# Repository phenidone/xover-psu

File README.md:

# Preamp Power Supply

This is a PCB design for an analogue preamplifier power supply

## Inputs

Power can be provided as one of:
* high voltage (240V) AC, relay-switched
* high voltage (240V) AC, unswitched,
* low voltage (20+20V) unregulated DC

An opto-isolated input (5-24V DC) is provided to control the power-switching relay.  Low-power (2A) switched AC loads can be
connected via terminals on the PCB, and high power loads (20A) can be switched using spade terminals on the rear of the 
relay.

If the PCB transformer is omitted, unregulated dual-rail DC can be fed into the linear regulator section.  Additional
filter capacitors may also be inserted at this point.  The unmute circuit will NOT work unless the transformer is present or
low-voltage AC is otherwise supplied to the board.

## Outputs

The circuit provides:
* +/- 12-15VDC, linear regulated
* 12VDC from always-on switchmode brick, for control circuits
* un-muting relay output
* 50Hz opto-isolated pulses for external power-sensing logic
* power-relay output

The power-relay terminals can be used as an output port to drive an external
relay, or can be used as an input port to drive the onboard relay if the
remote/relay driver circuit (U2, Q1, etc) is not populated.

The 12VDC output terminal could be used as an input from an external plugpack
if the HLK10M12 is not present.

### Unmute Logic

The UNMUTE output is designed to switch a 12V muting relay and thereby suppress bad noises that occur during power-up/down
brownout of preamplifier and power-amplifier circuits.

The unmute logic uses a slow turn-on RC timer and a fast turn-off RC timer, both of which are charged from opto-isolated pulses
derived from the mains transformer secondary.  The UNMUTE output (12VDC up to 500mA) is enabled after the slow timer charges, 
which is about 1s after power is applied; for a shorter turn-on delay, reduce the value of R2 and/or C1.

When power is withdrawn, the fast timer discharges in about 50ms, which causes Q2 to discharge the C in the slow timer,
thereby immediately shutting off the UNMUTE output and resetting the startup time.

Each RC timer uses a TL431 to provide a distinct transition point, for fast(ish) turn-on/off transitions.

A secondary AC pulse output is provided as bare optoisolator pins, allowing an external logic circuit to safely monitor the presence of AC
power going into the linear regulator.

### Linear Regulation

The dual-rail DC output is designed to power opamp-based preamplifier circuits and as such, has an output of approx 12-15V
DC depending on resistor selection choices.  The circuit should be good for about 250mA, depending on the transformer regulation.

## Construction

The board is very densely populated, and on both sides.  First assemble all the surface-mount components on the board front,
then install all through-hole components (except screw terminals) on the board rear.

### Errata

The pinouts of some TL431 devices have pins 1 and 2 reversed, i.e. they are mis-marked TL432s.  You can, with a little bending
of their leads, install those upside down and it will work.  The layout assumes the pin order is 1=K, 2=R, 3=A.

### Component Sourcing

The major/expensive items required are:
* TE T9GS1L24-12 power relay
* HiLink 10M12 AC/DC switchmode brick
* Vigortronix VTX-120-5412-415 transformer for 15V operation
    * alternative: VTX-120-5412-412 for 12V operation
    * alternative: Block PT-13/2/12 which has a similar footprint
* Bourns PM3700 common-mode choke
* Rectifier filter caps: Panasonic EEEFK 3300u or similar 18mm square electrolytics
* Other silicon and passives - buy it on eBay from China

An 0805 passive sample book is very handy for filling out most of the circuit; low-noise/precision values are not required.

### Output Voltage

Output voltage is selected by voltage dividers on the LM317 and LM337.  
Choose R18 and R28 to be 240R or 270R, then select values for R20 and R23
so that

> R20 = R18 (VOUT / 1.25 - 1)

If R20 is not a convenient value, make a parallel combination e.g. 5k1 and 6k8
in lieu of 3k to get about 15V.

### Regulator Caps

Regulator output capacitors should preferably be tantalum or aluminium electrolytic.
You can use either C6/C14 (SMD) or C7/C15 (through hole) footprints.  Make 
sure the capacitors are rated for notably more than the output voltage, 
e.g. 25V.

Ceramic caps here will cause regulator instability and oscillation.

### Pi Filter

The rectifier filter is a C-R-C pi-filter with 3300u per side.  Choose the resistors (R31, R26 etc) so that
the net voltage drop across them is as much as you can handle, without:
* bringing the unregulated DC rail so low that ripple breaks through the regulators, or
* the resistors overheating (max 100mW each) at your max design-load current

Larger resistors will provide greater ripple smoothing, at the expense of lower voltage
input to the regulators.  Choice will depend on your selection of transformer voltage, 
output voltage, and max expected load current.  A 15V supply has more room here for 
voltage drop (and therefore smoothing) than a 12V supply does.

Bridge them with 0R if you want a simple capacitor-only rectification filter.  Loading all
eight with 10R is probably OK for a 250mA output and will lose you about 0.65V DC and 160mW per rail.

### AC bits

The MOVs and common-mode choke are probably not critical.  Bridge over the 
choke if you're feeling EMI-antisocial, though this may result in HF conducted
EMI reaching your regulated outputs.

Use 500mA M205 slow blow glass fuses; there is one for each of the switchmode and
linear-regulated parts of the supply.  The switched-AC output is not fused, and should be good for 
about 5A before there are issues with terminal blocks.  For switching high-power amplifiers, use the
spade connectors on the rear of the relay.

### Grounding

There are three separate grounds:
* AGND, the centre of the dual-regulated supply
* DGND, ground for the 12V VDD switchmode/logic/control supply
* EARTH, a chassis safety connection

AGND is connected to EARTH via four opposed diodes in a bridge configuration,
which will keep them to no more than about 1.4V apart, but otherwise uncoupled
with respect to noise.

DGND is connected to EARTH via two opposed diodes and a capacitor.  They may
be up to 0.7V apart, and noise from the DC side of the 10M12 should be 
conducted into EARTH via C18.  These ground-lift circuits should be strong 
enough to trip an ELCB if there is a transformer-isolation fault that brings
mains AC power to the low voltage side.

The Vigortronix transformers have exposed steel cores which must be grounded via
mounting screws through the PCB, which are connected via the PCB to the 
EARTH screw terminal.

### PCB

Use a full-thickness (16.mm) PCB; 1mm boards are too flimsy with all of the heavy power supply components mounted.

## TRL and Regulatory

This design is tested and working in a benign environment at Rev.A.  It has not faced MTBF validation,
environmental (thermal+vibration) or EMI compliance testing.

In terms of electrical safety, this design
* is intended for use in Class I (grounded) equipment:
    * a safety-ground connection is mandatory,
    * it must be installed inside an IEC-60950 grounded case per Class I;
* additionally aims to comply with IEC-60950 "reinforced insulation" creepage+clearance rules,
* uses diode-based ground-lift circuits that may not be legal in all jurisdictions for a Class I device,

The design has not been certified by any regulatory body or independent third party testing agency.  You must 
not sell any product containing this power supply without first obtaining certification.

## License

This hardware design is (C) 2021 William Brodie-Tyrrell and is licensed under the CERN OHL; see cern_ohl_v_1_2.pdf

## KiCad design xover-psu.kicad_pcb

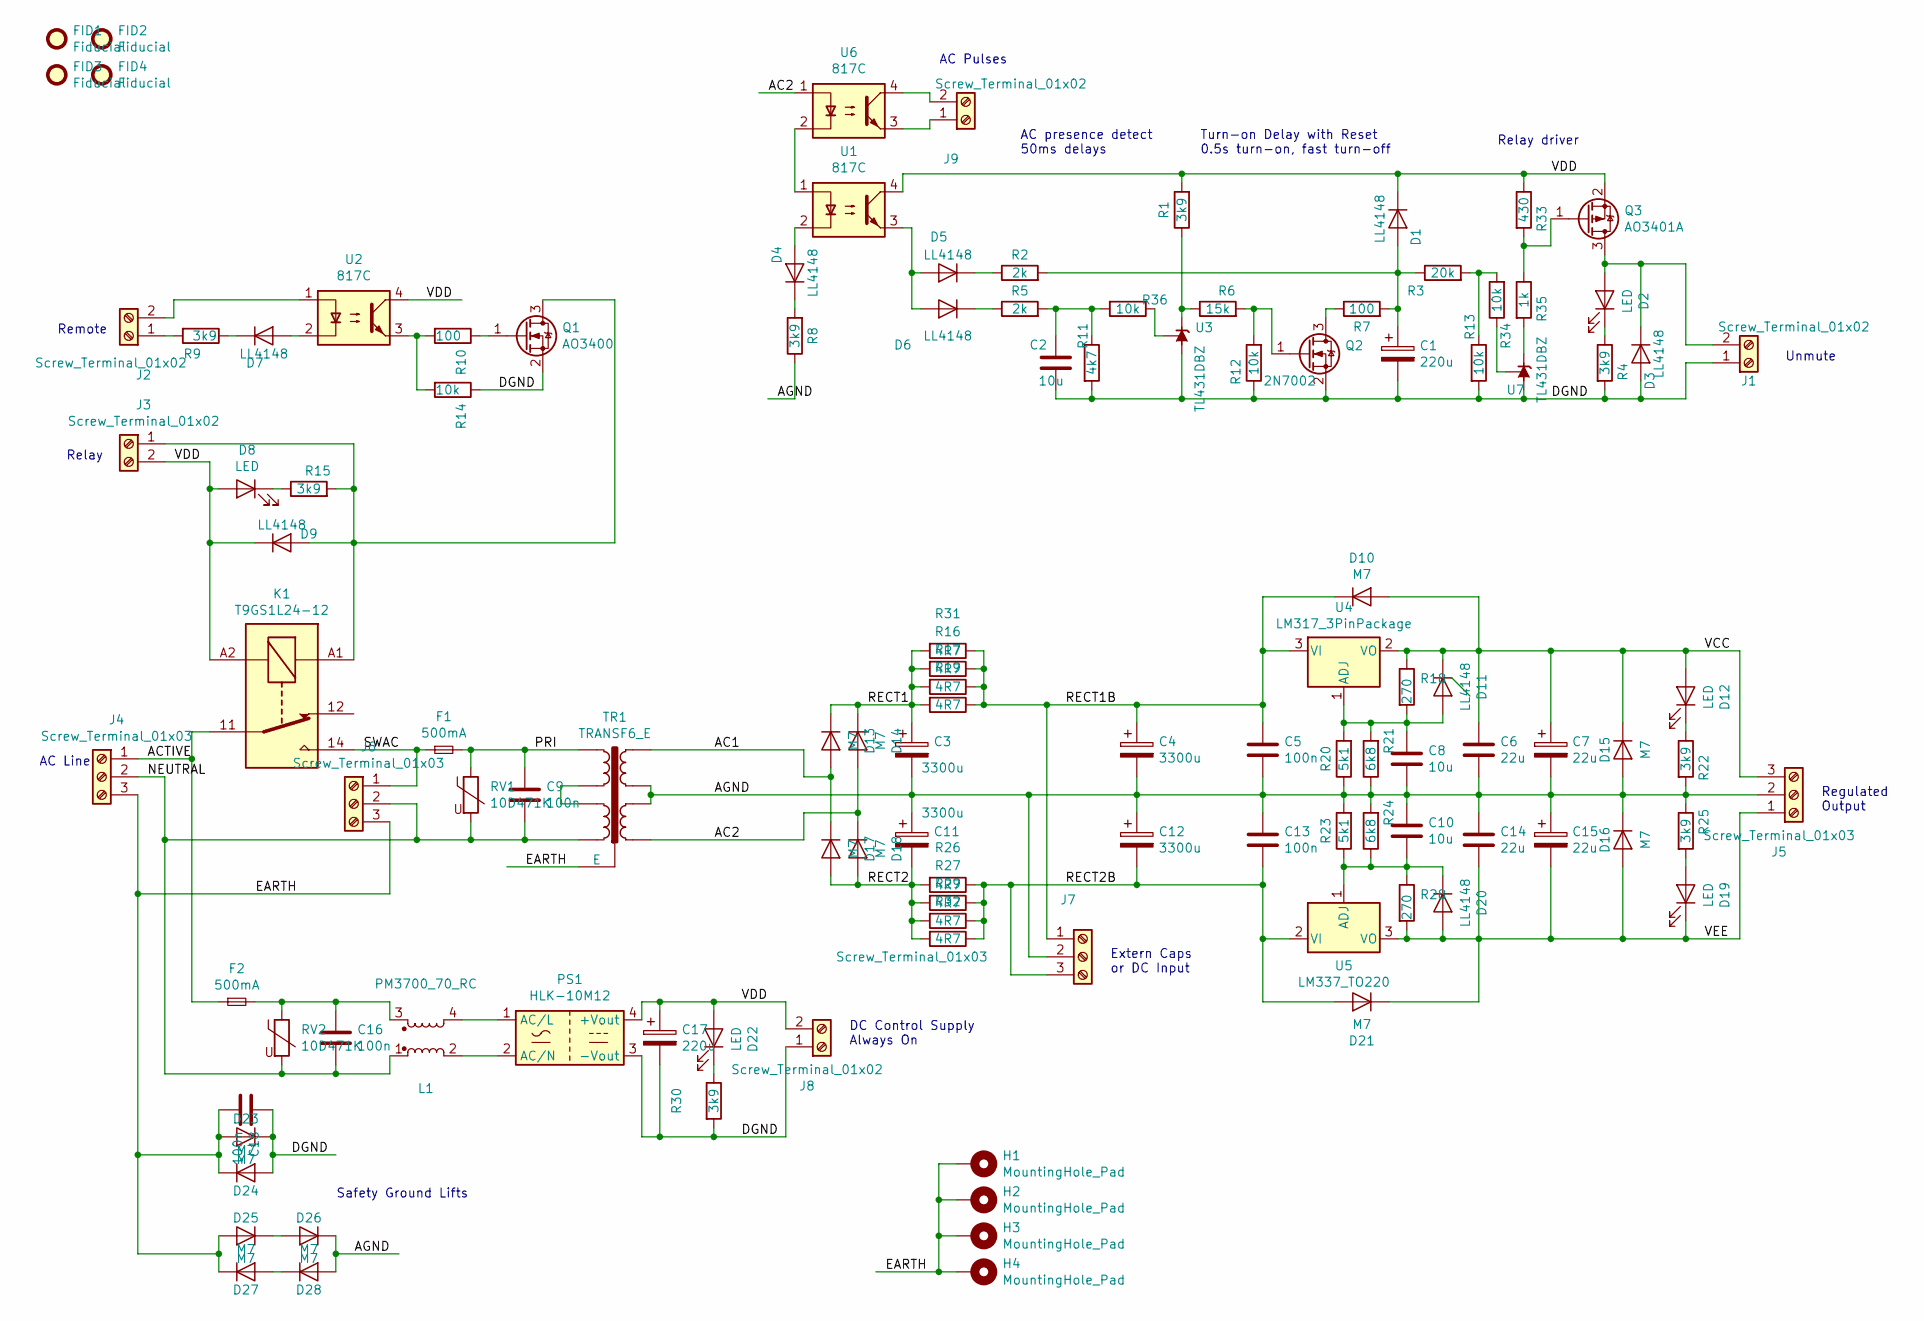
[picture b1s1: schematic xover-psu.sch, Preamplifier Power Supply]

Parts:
C1, C17: 220u; CP_Elec_10x10; MFG Part Num EEEFP1H221AP
C2, C8, C10: 10u; C_1210
C3, C4, C11, C12: 3300u; CP_Elec_EEEFK-K16
C5, C13, C18: 100n; C_0805
C6, C14: 22u; C_1210_HandSoldering
C7, C15: 22u; CP_Radial_Tantal_D6.0mm_P5.00mm
C9, C16: 100n; C_Rect_L18.0mm_W6.0mm_P15.00mm_FKS3_FKP3; MFG Part Num ECQU2A104KLA
D1, D3, D4, D5, D6, D7, D9, D11, D20: LL4148; D_MiniMELF
D2, D8, D12, D19, D22: LED; LED_0805
D10, D13, D14, D15, D16, D17, D18, D21, D23, D24, D25, D26, D27, D28: M7; D_SMA
F1, F2: 500mA; Fuseholder5x20_6mm
FID1, FID2, FID3, FID4: Fiducial; Fiducial_1mm_Dia_2.54mm_Outer_CopperTop
H1, H2, H3, H4: MountingHole_Pad; MountingHole_3.2mm_M3_DIN965_Pad
J1, J2, J3, J8, J9: Screw_Terminal_01x02; TerminalBlock_Phoenix_MKDS1.5-2pol
J4, J5, J6, J7: Screw_Terminal_01x03; TerminalBlock_Phoenix_MKDS1.5-3pol
K1: T9GS1L24-12; Potter_T9G_Relay
L1: PM3700_70_RC; PM3700
PS1: HLK-10M12
Q1: AO3400; SOT-23
Q2: 2N7002; SOT-23
Q3: AO3401A; SOT-23
R1, R4, R8, R9, R15, R22, R25, R30: 3k9; R_0805
R2, R5: 2k; R_0805
R3: 20k; R_0805
R6: 15k; R_0805
R7, R10: 100; R_0805
R11: 4k7; R_0805
R12, R13, R14, R34, R36: 10k; R_0805
R16, R17, R19, R26, R27, R29, R31, R32: 4R7; R_0805
R18, R28: 270; R_0805
R20, R23: 5k1; R_0805
R21, R24: 6k8; R_0805
R33: 430; R_0805
R35: 1k; R_0805
RV1, RV2: 10D471K; RV_Disc_D12_W3.9_P7.5
TR1: TRANSF6_E; Trafo_CHK-EI54-12VA_Combo_Vigor
U1, U2, U6: 817C; DIP-4_W7.62mm
U3, U7: TL431DBZ; SOT-23
U4: LM317_3PinPackage; TO-220-3_Vertical
U5: LM337_TO220; TO-220-3_Vertical

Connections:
/AC1: D13.2 (A), D17.1 (K), TR1.5
/AC2: D14.2 (A), D18.1 (K), TR1.8, U6.1
/ACTIVE: F2.1, J4.1, K1.11
/AGND: C3.2, C4.2, C5.2, C6.2, C7.2, C8.2, C10.1, C11.1, C12.1, C13.1, C14.1, C15.1, D15.2 (A), D16.1 (K), D26.1 (K), D28.2 (A), J5.2, J7.2, R8.1, R20.1, R21.1, R22.2, R23.2, R24.2, R25.1, TR1.6, TR1.7
/DGND: C1.2, C2.2, C17.2, C18.1, D3.2 (A), D23.1 (K), D24.2 (A), J1.1, J8.1, PS1.3 (-Vout), Q1.2 (S), Q2.2 (S), R4.2, R11.2, R12.1, R13.2, R14.1, R30.2, U3.3 (A), U7.3 (A)
/EARTH: C18.2, D23.2 (A), D24.1 (K), D25.2 (A), D27.1 (K), H1.1, H2.1, H3.1, H4.1, J4.3, J6.3, TR1.E
/NEUTRAL: C9.2, C16.2, J4.2, J6.2, L1.1, RV1.2, RV2.2, TR1.1
/PRI: C9.1, F1.2, RV1.1, TR1.4
/RECT1: C3.1, D13.1 (K), D14.1 (K), R16.2, R17.2, R19.2, R31.2
/RECT1B: C4.1, C5.1, D10.1 (K), J7.1, R16.1, R17.1, R19.1, R31.1, U4.3 (VI)
/RECT2: C11.2, D17.2 (A), D18.2 (A), R26.2, R27.2, R29.2, R32.2
/RECT2B: C12.2, C13.2, D21.2 (A), J7.3, R26.1, R27.1, R29.1, R32.1, U5.2 (VI)
/SWAC: F1.1, J6.1, K1.14
/VCC: C6.1, C7.1, D10.2 (A), D11.1 (K), D12.2 (A), D15.1 (K), J5.3, R18.1, U4.2 (VO)
/VDD: C17.1, D1.1 (K), D8.2 (A), D9.1 (K), D22.2 (A), J3.2, J8.2, K1.A2, PS1.4 (+Vout), Q3.2 (S), R1.2, R33.1, U1.4, U2.4
/VEE: C14.2, C15.2, D16.2 (A), D19.1 (K), D20.2 (A), D21.1 (K), J5.1, R28.2, U5.3 (VO)
unnamed: C1.1, D1.2 (A), R2.2, R3.1, R7.2
unnamed: C2.1, R5.2, R11.1, R36.2
unnamed: C8.1, D11.2 (A), R18.2, R20.2, R21.2, U4.1 (ADJ)
unnamed: C10.2, D20.1 (K), R23.1, R24.1, R28.1, U5.1 (ADJ)
unnamed: C16.1, F2.2, L1.3, RV2.1
unnamed: D2.1 (K), R4.1
unnamed: D2.2 (A), D3.1 (K), J1.2, Q3.3 (D)
unnamed: D4.1 (K), R8.2
unnamed: D4.2 (A), U1.2
unnamed: D5.1 (K), R2.1
unnamed: D5.2 (A), D6.2 (A), U1.3
unnamed: D6.1 (K), R5.1
unnamed: D7.1 (K), R9.1
unnamed: D7.2 (A), U2.2
unnamed: D8.1 (K), R15.1
unnamed: D9.2 (A), J3.1, K1.A1, Q1.3 (D), R15.2
unnamed: D12.1 (K), R22.1
unnamed: D19.2 (A), R25.2
unnamed: D22.1 (K), R30.1
unnamed: D25.1 (K), D26.2 (A)
unnamed: D27.2 (A), D28.1 (K)
unnamed: J2.1, R9.2
unnamed: J2.2, U2.1
unnamed: J9.1, U6.3
unnamed: J9.2, U6.4
unnamed: L1.2, PS1.2 (AC/N)
unnamed: L1.4, PS1.1 (AC/L)
unnamed: Q1.1 (G), R10.1
unnamed: Q2.1 (G), R6.2, R12.2
unnamed: Q2.3 (D), R7.1
unnamed: Q3.1 (G), R33.2, R35.1
unnamed: R1.1, R6.1, U3.1 (K)
unnamed: R10.2, R14.2, U2.3
unnamed: R3.2, R13.1, R34.2
unnamed: R34.1, U7.2 (REF)
unnamed: R35.2, U7.1 (K)
unnamed: R36.1, U3.2 (REF)
unnamed: TR1.2, TR1.3
unnamed: U1.1, U6.2

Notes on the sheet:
Regulated Output
DC Control Supply Always On
Relay
AC Line
Remote
Turn-on Delay with Reset 0.5s turn-on, fast turn-off
Relay driver
AC presence detect 50ms delays
Safety Ground Lifts
Extern Caps or DC Input
Unmute
AC Pulses

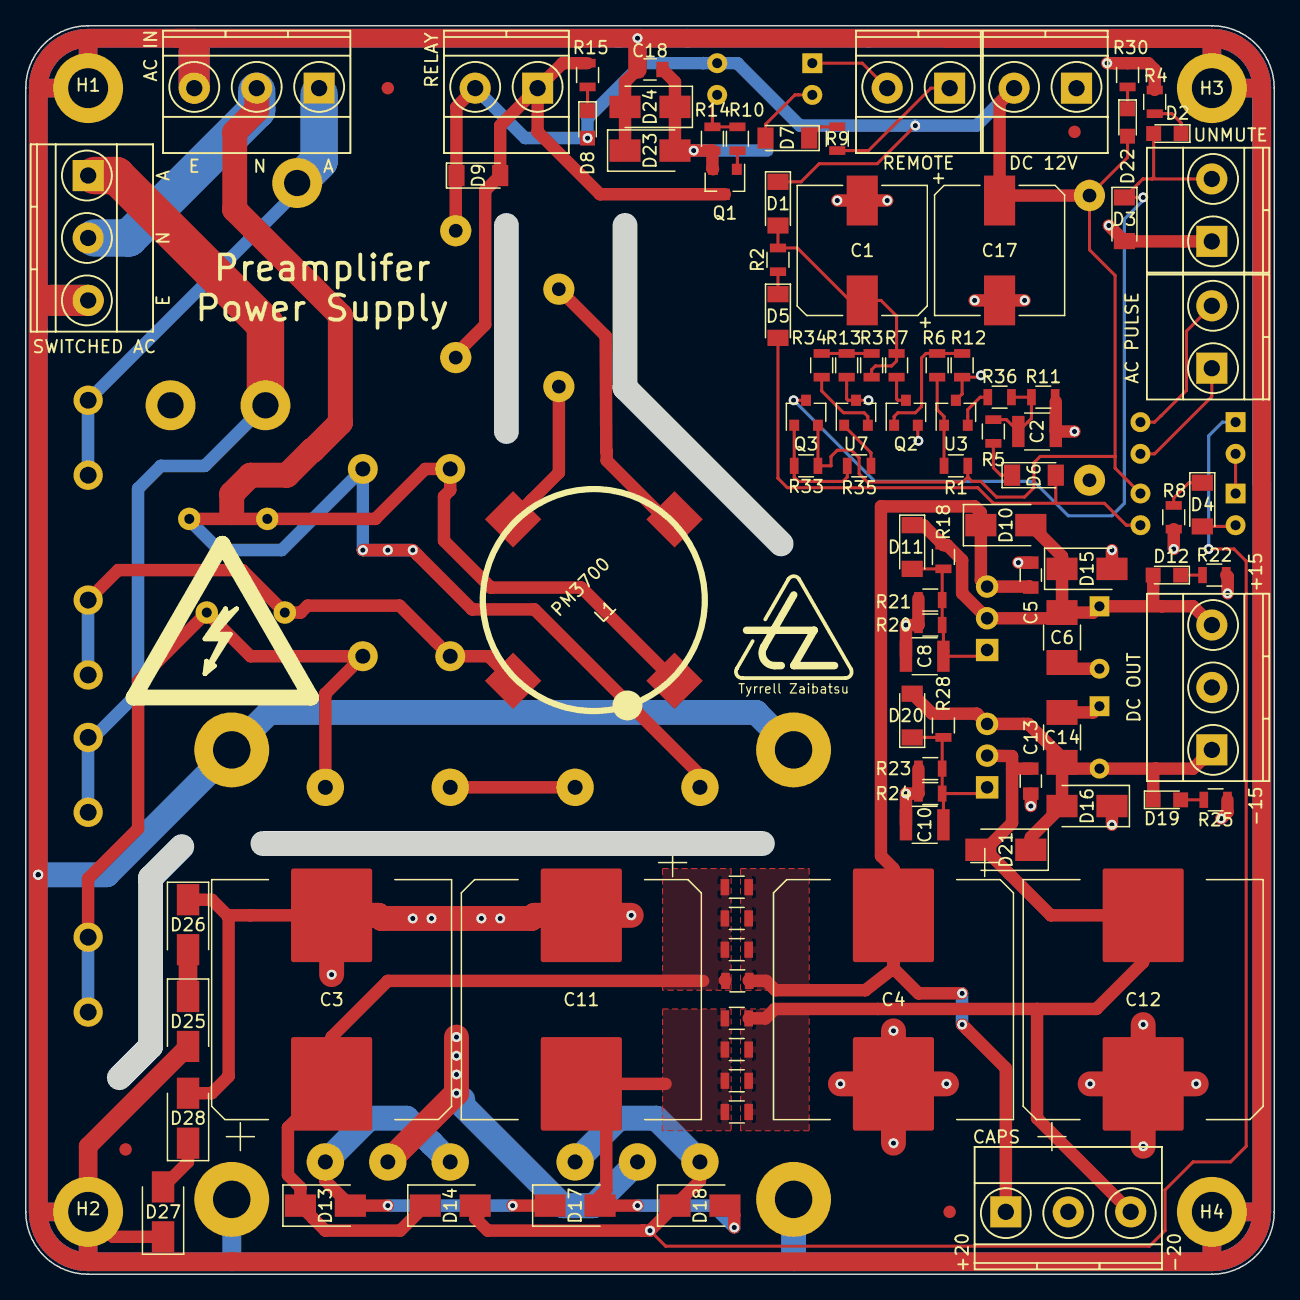
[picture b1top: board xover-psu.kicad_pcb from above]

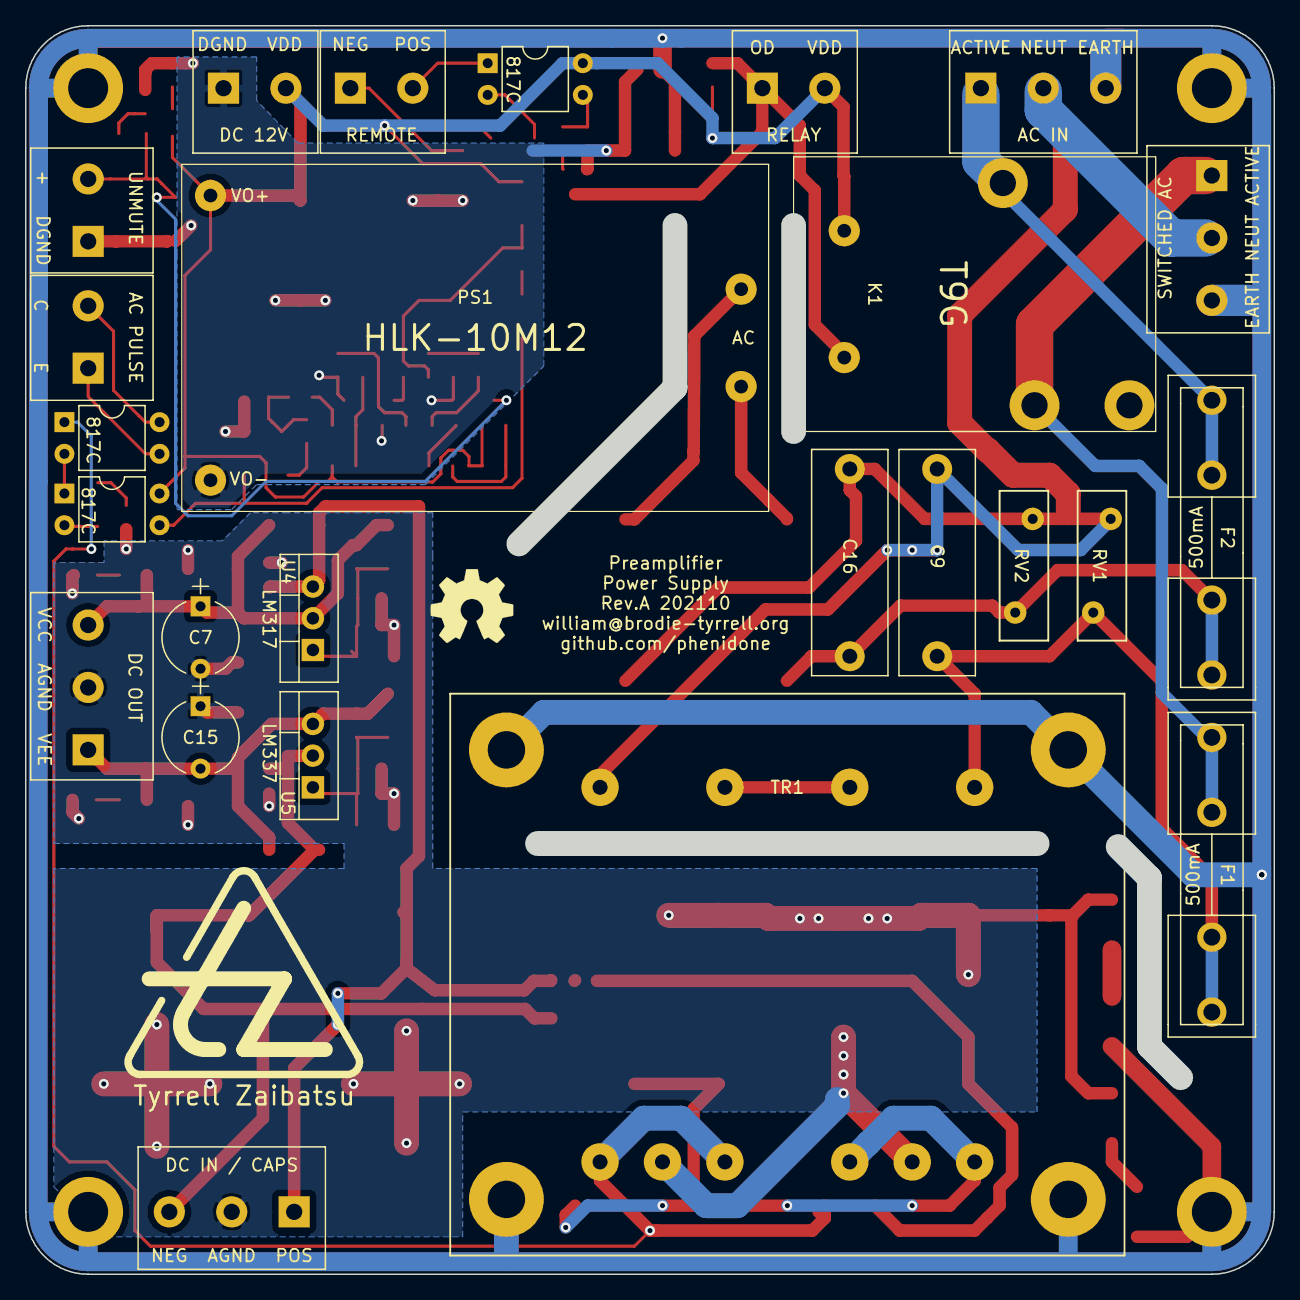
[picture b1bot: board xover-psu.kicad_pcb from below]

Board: 2 copper layers, 98.1 x 98.1 mm, 117 parts (16 on the bottom side), 55 nets.

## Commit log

2021-10-07 Textbook two-rail linear regulator with LM317 etc.
2021-10-09 Added unmute-timing draft schematic (mostly FETs, untested)
2021-10-09 Converted unmute circuit to TL431 for distinct turn-on/off behaviour
2021-10-09 fixed readme
2021-10-09 Created PDF schematic
2021-10-10 improved TL431 biasing, higher-ESR filter cap options for stability
2021-10-10 defined all the custom footprints
2021-10-12 Completed placement (no routing) on layout
2021-10-14 First pass routing completed for all but the UNMUTE timer/logic
2021-10-14 Fixed transformer phase, made some mains tracks fatter
2021-10-15 prettified everything - round corners, readable silkscreens, etc.
2021-10-15 better AGND plane divide, regenerated layout png
2021-10-25 updated schematic for faster turn-on transition for UNMUTE
2021-10-26 tested UNMUTE circuit, improved switch-on/off speed, rejigged mains routing for EMI
2021-10-28 taped out, updated README
2021-12-14 updated README to show tested-as-working, plus regulatory details
